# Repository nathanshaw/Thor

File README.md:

# Thor
The largest of the Pantheon Actuator Controller boards - 48 outputs (3 banks of 16), RGB LED, 3x I2C inputs

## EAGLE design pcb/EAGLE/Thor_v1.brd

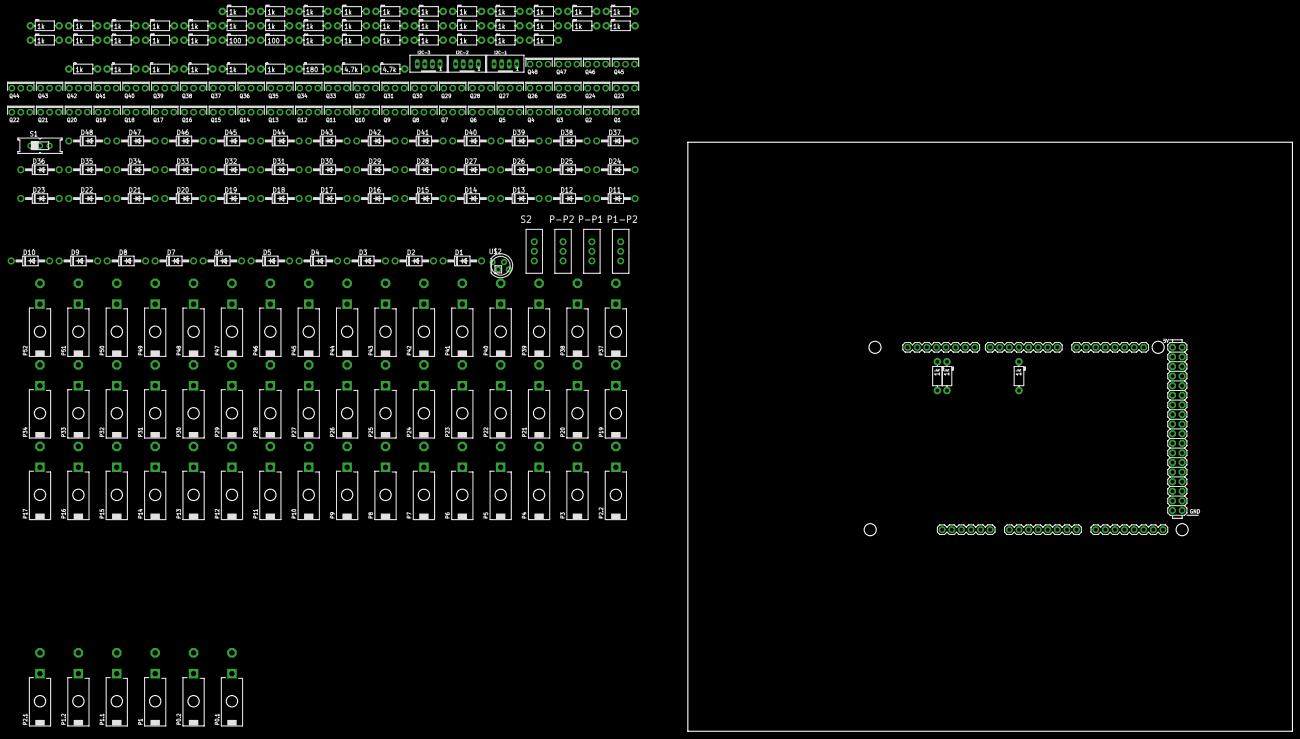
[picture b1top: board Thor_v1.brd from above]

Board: 2 copper layers, 160.0 x 155.9 mm, 213 parts (0 on the bottom side), 158 nets, no tracks yet.

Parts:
D1, D2, D3, D4, D5, D6, D7, D8, D9, D10, D11, D12, D13, D14, D15, D16, D17, D18, D19, D20, D21, D22, D23, D24, D25, D26, D27, D28, D29, D30, D31, D32, D33, D34, D35, D36, D37, D38, D39, D40, D41, D42, D43, D44, D45, D46, D47, D48: 1N4004; DO41-10
I2C-1, I2C-2, I2C-3: JST-PH_4-PIN_HEADER; JST_B4B-PH_HEADER
P0.1, P0.2, P1, P1.1, P1.2, P2.1, P2.2, P3, P4, P5, P6, P7, P8, P9, P10, P11, P12, P13, P14, P15, P16, P17, P19, P20, P21, P22, P23, P24, P25, P26, P27, P28, P29, P30, P31, P32, P33, P34, P37, P38, P39, P40, P41, P42, P43, P44, P45, P46, P47, P48, P49, P50, P51, P52: 39-30-02?; 39-30-?02?
P1-P2: SWITCH-SPDT
P-P1, P-P2: SWITCH-SPDT
Q1, Q2, Q3, Q4, Q5, Q6, Q7, Q8, Q9, Q10, Q11, Q12, Q13, Q14, Q15, Q16, Q17, Q18, Q19, Q20, Q21, Q22, Q23, Q24, Q25, Q26, Q27, Q28, Q29, Q30, Q31, Q32, Q33, Q34, Q35, Q36, Q37, Q38, Q39, Q40, Q41, Q42, Q43, Q44, Q45, Q46, Q47, Q48: T460; TO225AAV
R1, R2: 4.7k; AXIAL-0.3-KIT
R3: 180; AXIAL-0.3-KIT
R4, R5, R6, R7, R8, R9, R10, R11, R12, R13, R14, R15, R16, R17, R18, R19, R22, R23, R24, R25, R26, R27, R28, R29, R30, R31, R32, R33, R34, R35, R36, R37, R38, R39, R40, R41, R42, R43, R44, R45, R46, R47, R48, R49, R50, R51, R52, R53: 1k; AXIAL-0.3-KIT
R20, R21: 100; AXIAL-0.3-KIT
S1: EG1218
S2: SWITCH-SPDT
U2: ARDUINO-MEGAMIN_SILK; ARDUINO_MEGA_MIN_SILK_NO_OUTLINE
U$2: RGBLED_CA; LED5MMRGB

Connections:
3.3V: S1.O, U2.3.3V
5V: I2C-1.P4, I2C-2.P4, I2C-3.P4, R1.P$2, R2.P$1, S1.S, U2.5V@1, U2.5V@2
22: R15.P$1, U2.22
23: R22.P$1, U2.23
24: R23.P$1, U2.24
26: R25.P$1, U2.26
27: R26.P$1, U2.27
28: R27.P$1, U2.28
29: R28.P$1, U2.29
30: R29.P$1, U2.30
31: R30.P$1, U2.31
32: R31.P$1, U2.32
33: R32.P$1, U2.33
34: R33.P$1, U2.34
35: R34.P$1, U2.35
36: R35.P$1, U2.36
37: R36.P$1, U2.37
38: R37.P$1, U2.38
39: R53.P$1, U2.39
40: R38.P$1, U2.40
41: R39.P$1, U2.41
42: R40.P$1, U2.42
43: R41.P$1, U2.43
47: R42.P$1, U2.47
48: R43.P$1, U2.48
49: R44.P$1, U2.49
50: R45.P$1, U2.50
51: R46.P$1, U2.51
52: R47.P$1, U2.52
53: R48.P$1, U2.53
A0: R3.P$1, U2.A0, U$2.4
A2: R20.P$1, R49.P$1, U2.A2, U$2.1
A3: R50.P$1, U2.A3
A4: R51.P$1, U2.A4
A5: R52.P$1, U2.A5
ARDUINO_GND: U2.GND@2, U$2.2
GND: I2C-1.P1, I2C-2.P1, I2C-3.P1, P0.1.2, P0.2.2, Q1.2, Q2.2, Q3.2, Q4.2, Q5.2, Q6.2, Q7.2, Q8.2, Q9.2, Q10.2, Q11.2, Q12.2, Q13.2, Q14.2, Q15.2, Q16.2, U2.GND@3, U2.GND@4
GND1: P1.1.2, P1.2.2, Q31.2, Q32.2, Q33.2, Q34.2, Q35.2, Q36.2, Q37.2, Q38.2, Q39.2, Q40.2, Q41.2, Q42.2, Q43.2, Q44.2, Q45.2, Q46.2, Q47.2, Q48.2
GND2: P2.1.2, P2.2.2, Q17.2, Q18.2, Q19.2, Q20.2, Q21.2, Q22.2, Q23.2, Q24.2, Q25.2, Q26.2, Q27.2, Q28.2, Q29.2, Q30.2
unnamed: R21.P$1, U$2.3
unnamed: D2.A, P3.2, Q1.1
unnamed: D17.A, P19.2, Q17.1
unnamed: D1.A, P1.2, Q2.1
unnamed: D18.A, P20.2, Q18.1
unnamed: Q1.3, R19.P$2
unnamed: Q18.3, R22.P$2
unnamed: U2.17, U2.25
unnamed: Q2.3, R4.P$2
unnamed: D3.A, P4.2, Q3.1
unnamed: D19.A, P21.2, Q19.1
unnamed: Q19.3, R23.P$2
unnamed: Q3.3, R5.P$2
unnamed: D4.A, P5.2, Q4.1
unnamed: D20.A, P22.2, Q20.1
unnamed: Q4.3, R6.P$2
unnamed: D5.A, P6.2, Q8.1
unnamed: Q20.3, R24.P$2
unnamed: D21.A, P23.2, Q24.1
unnamed: Q8.3, R7.P$2
unnamed: D6.A, P7.2, Q7.1
unnamed: Q24.3, R25.P$2
unnamed: D22.A, P24.2, Q23.1
unnamed: Q7.3, R8.P$2
unnamed: D7.A, P8.2, Q6.1
unnamed: Q6.3, R9.P$2
unnamed: D8.A, P9.2, Q5.1
unnamed: Q23.3, R26.P$2
unnamed: Q5.3, R10.P$2
unnamed: D9.A, P10.2, Q12.1
unnamed: D23.A, P25.2, Q22.1
unnamed: Q22.3, R27.P$2
unnamed: Q12.3, R11.P$2
unnamed: D10.A, P11.2, Q11.1
unnamed: D24.A, P26.2, Q21.1
unnamed: Q21.3, R28.P$2
unnamed: Q11.3, R12.P$2
unnamed: D11.A, P12.2, Q10.1
unnamed: D25.A, P27.2, Q28.1
unnamed: Q28.3, R29.P$2
unnamed: Q10.3, R13.P$2
unnamed: D12.A, P13.2, Q9.1
unnamed: D26.A, P28.2, Q27.1
unnamed: Q27.3, R30.P$2
unnamed: Q9.3, R14.P$2
unnamed: D13.A, P14.2, Q16.1
unnamed: D27.A, P29.2, Q26.1
unnamed: Q26.3, R31.P$2
unnamed: Q16.3, R15.P$2
unnamed: D14.A, P15.2, Q15.1
unnamed: D28.A, P30.2, Q25.1
unnamed: Q25.3, R32.P$2
unnamed: Q15.3, R16.P$2
unnamed: D15.A, P16.2, Q14.1
unnamed: D29.A, P31.2, Q32.1
unnamed: Q32.3, R33.P$2
unnamed: Q14.3, R17.P$2
unnamed: D16.A, P17.2, Q13.1
unnamed: D30.A, P32.2, Q31.1
unnamed: Q31.3, R34.P$2
unnamed: Q13.3, R18.P$2
unnamed: D31.A, P33.2, Q30.1
unnamed: Q30.3, R35.P$2
unnamed: D32.A, P34.2, Q29.1
unnamed: Q29.3, R36.P$2
unnamed: Q17.3, R37.P$2
unnamed: D33.A, P37.2, Q33.1
unnamed: D34.A, P38.2, Q34.1
unnamed: Q34.3, R38.P$2
unnamed: D35.A, P39.2, Q35.1
unnamed: Q35.3, R39.P$2
unnamed: D36.A, P40.2, Q36.1
unnamed: Q36.3, R40.P$2
unnamed: D37.A, P41.2, Q40.1
unnamed: Q40.3, R41.P$2
unnamed: D38.A, P42.2, Q39.1
unnamed: Q39.3, R42.P$2
unnamed: D39.A, P43.2, Q38.1
unnamed: Q38.3, R43.P$2
unnamed: D40.A, P44.2, Q37.1
unnamed: Q37.3, R44.P$2
unnamed: D41.A, P45.2, Q44.1
unnamed: Q44.3, R45.P$2
unnamed: D42.A, P46.2, Q43.1
unnamed: Q43.3, R46.P$2
unnamed: D43.A, P47.2, Q42.1
unnamed: Q42.3, R47.P$2
unnamed: D44.A, P48.2, Q41.1
unnamed: Q41.3, R48.P$2
unnamed: D45.A, P49.2, Q48.1
unnamed: Q48.3, R49.P$2
unnamed: D46.A, P50.2, Q47.1
unnamed: Q47.3, R50.P$2
unnamed: D47.A, P51.2, Q46.1
unnamed: Q46.3, R51.P$2
unnamed: D48.A, P52.2, Q45.1
unnamed: Q45.3, R52.P$2
unnamed: Q33.3, R53.P$2
PW0: R14.P$1, U2.2
PW1: R13.P$1, U2.3
PW2: R12.P$1, U2.4
PW3: R19.P$1, U2.5
PW4: R4.P$1, U2.6
PW5: R5.P$1, U2.7
PW6: R6.P$1, U2.8
PW7: R7.P$1, U2.9
PW8: R8.P$1, U2.10
PW9: R11.P$1, U2.11
PW10: R10.P$1, U2.12
PW11: R9.P$1, U2.13
PW12: R18.P$1, U2.44
PW13: R17.P$1, U2.45
PW14: R16.P$1, U2.46
PWR: D1.C, D2.C, D3.C, D4.C, D5.C, D6.C, D7.C, D8.C, D9.C, D10.C, D11.C, D12.C, D13.C, D14.C, D15.C, D16.C, P0.1.1, P0.2.1, P1.1, P3.1, P4.1, P5.1, P6.1, P7.1, P8.1, P9.1, P10.1, P11.1, P12.1, P13.1, P14.1, P15.1, P16.1, P17.1, P-P1.2, P-P2.2, S2.2
PWR1: D29.C, D33.C, D34.C, D35.C, D36.C, D37.C, D38.C, D39.C, D40.C, D41.C, D42.C, D43.C, D44.C, D45.C, D46.C, D47.C, D48.C, P1-P2.2, P1.1.1, P1.2.1, P31.1, P37.1, P38.1, P39.1, P40.1, P41.1, P42.1, P43.1, P44.1, P45.1, P46.1, P47.1, P48.1, P49.1, P50.1, P51.1, P52.1, P-P1.1
PWR2: D17.C, D18.C, D19.C, D20.C, D21.C, D22.C, D23.C, D24.C, D25.C, D26.C, D27.C, D28.C, D30.C, D31.C, D32.C, P1-P2.1, P2.1.1, P2.2.1, P19.1, P20.1, P21.1, P22.1, P23.1, P24.1, P25.1, P26.1, P27.1, P28.1, P29.1, P30.1, P32.1, P33.1, P34.1, P-P2.1
SCL: I2C-1.P2, I2C-2.P2, I2C-3.P2, R2.P$2, U2.21
SDA: I2C-1.P3, I2C-2.P3, I2C-3.P3, R1.P$1, U2.20
VIN: S2.1, U2.VIN

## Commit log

2017-02-15 init commit
2017-03-16 more work on initial design

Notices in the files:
parts and their libraries:
SparkFun-Electromechanical: Licensing: Creative Commons ShareAlike 4.0 International - https://creativecommons.org/licenses/by-sa/4.0
con-molex-mini-fit: Copyright (C) 2011, Bob Starr
